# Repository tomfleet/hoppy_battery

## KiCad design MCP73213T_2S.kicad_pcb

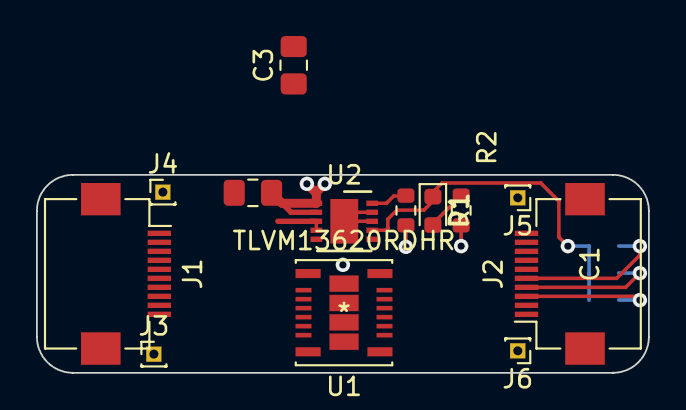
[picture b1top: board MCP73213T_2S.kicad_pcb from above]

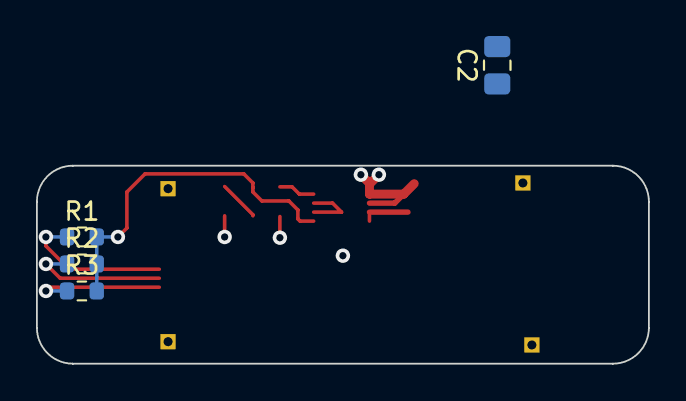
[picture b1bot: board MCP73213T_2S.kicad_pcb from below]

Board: 2 copper layers, 34.0 x 11.0 mm, 17 parts (4 on the bottom side), 13 nets.

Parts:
C1, C2, C3: C_Small; C_0805_2012Metric_Pad1.18x1.45mm_HandSolder
D1: LED; LED_0603_1608Metric
J1, J2: Conn_01x10; Hirose_FH12-10S-0.5SH_1x10-1MP_P0.50mm_Horizontal
J3, J4, J5, J6: Conn_01x01_Female; PinHeader_1x01_P1.00mm_Vertical
R1, R1#2, R2, R2#2, R3: R_Small; R_0603_1608Metric
U1: TLVM13620RDHR
U2: MCP73213T; DFN-10-1EP_3x3mm_P0.5mm_EP1.55x2.48mm

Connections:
GND: C1.2, C2.2, C3.2, J1.9, J1.10, J2.1, J2.2, J6.1, R1.2, U2.8 (VSS), U2.9 (VSS), U2.11 (EP)
unnamed: C2.1, J4.1, J5.1
unnamed: C3.1, J3.1, U2.3 (VBATT), U2.4 (VBATT)
unnamed: D1.2 (A), R2.1
unnamed: J1.3, J2.8
unnamed: J1.4, J2.7
unnamed: J1.5, J2.6
unnamed: J1.6, J2.5
unnamed: J1.7, J2.4
unnamed: J1.8, J2.3
unnamed: R1.1, U2.10 (PROG)
STAT: D1.1 (K), R1#2.2, R2#2.2, R3.2, U2.7 (STAT)
VDD: C1.1, J1.1, J1.2, J2.9, J2.10, R2.2, U2.1 (VDD), U2.2 (VDD)

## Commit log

2022-06-28 added power module

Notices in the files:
parts and their libraries:
Copyright 2021 Accelerated Designs. All rights reserved.
